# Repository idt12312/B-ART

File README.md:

# 概要
B-ARTはXbee ZigBeeモジュールみたいにUARTを無線で飛ばすモジュールです。
マイコンのプログラムを追加で書くことなく、UARTのTXとRXだけをつなげるだけでUARTを無線化できます。
無線部分はBLE(Bluetooth Low Energy)で実装をしています。

非常に小さいことが特徴で、**開発中の基板に挿して簡単に使える無線モジュール**をコンセプトに開発をしています。
(現状、秋月で買えるどの無線モジュールよりも小さいはず)

B-ARTにはType-PとType-Uの2種類があり、Type-Pはピンヘッダ、Type-UはUSBコネクタがついています。
Type-Pには4pinのピンヘッダが付いていて、3.3V-GND-TX-RX
の4本を接続するだけで使うことができます。
Type-UにはPCに直接挿せるUSBコネクタと、FTDIのUSB-UART変換IC(FT234XD)が載っています。
FT234XDのおかげでPCにさすとシリアルポートとして認識されるので、
普段シリアルポートを使うときと全く変わることなく使うことができます。

B-ARTの裏面にはType-P、Type-UともにDIPスイッチがあり、そこからIDを設定できます。
IDが同じ相手を選択して通信をするので、同じ環境にB-ARTが何組もあってもIDさえ違えば混線が起きないようになっています。

## 使用例
例えば小さい走行ロボットを無線を使ってデバッグする時にB-ARTは役立つでしょう。
走行をさせるときに有線だと線が邪魔になり、Xbeeなどはモジュールが大きすぎて載せられないという状況です。

下の写真は現在制作中のマイクロマウスの機体[MIZUHOv2](http://idken.net/posts/2017-04-01-mizuhov2/)に
B-ART TypePを挿しているところです。

B-ARTは非常に小さく軽いので、マイクロマウスの機体に乗せても走行時にそれほど問題にはなりません。
基板に4pinのコネクタさえつけておけばほしい時にだけB-ARTを挿して使うことができます。

# 使い方

## DIPスイッチの設定

B-ARTのType-PとType-Uの基板の裏にはDIPスイッチが4bit分あり、
1bitはクライアント動作をするかサーバー動作をするか、3bitはIDを意味していています。

| DIPスイッチ | 意味                     |
|-------------|--------------------------|
| 1           | 0:client動作  1:server動作 |
| 2           | ID  bit2                   |
| 3           | ID  bit1                   |
| 4           | ID  bit0                   |

B-ARTは通信においてはType-PであるかType-Uであるかは関係なく、
同じIDを持つサーバーとクライアントが1対1で通信できるという仕組みになっています。
なので、同じIDを持っていさえすれば、

* TypeU <-> TypeU
* TypeP <-> TypeP
* TypeU <-> TypeP

の全ての組み合わせで通信が可能です。

## TypePのセットアップ
4pinのピンヘッダ(というよりスルーホール)があり、それぞれのpinは次のような意味を持っています。

B-ARTは最大30mAくらいの電流を必要とするので、それに耐えられるような電源につないでください。

**電源・IOの電圧は3.3Vであることに注意してください**

## TypeUのセットアップ
パソコンのUSBに挿すだけです。

## 電源を入れる
電源を入れると
クライアント動作に設定されているB-ARTは赤色LEDが、
サーバー動作に設定されているB-ARTは緑色のLEDが光ります。

## サーバーとクライアントの接続
サーバー側とクライアント側に同じIDを持たせた状態で電源を入れると自動的に接続されます。
接続された瞬間にB-ARTに乗っている緑と赤の両方のLEDが一瞬点滅します。

一旦切断されても、接続可能な状態になると自動で接続されます。

## データを送受信する
UARTにデータを流すとサーバー側、クライアント側どちらからでももう片方に送信されます。
その際にLEDが点滅するので、LEDを見ることで正常に動作しているかが分かります。

### UARTの通信仕様

以下の設定でのみ動作します。

| パラメータ     | 値 |
|--------------|-----------|
| Baudrate     | 115200bps |
| Data size    | 8bit      |
| Start bit    | 1bit      |
| Stop bit     | 1bit      |
| Parity       | なし       |
| Flow control | なし       |
| 信号レベル      | 3.3V      |

※UART側からデータを連続して送り続けると、データが欠損する可能性があります。
確実に連続して送信できるのは70byteくらいです。
それ以上のデータが連続する場合は、70byteくらいごとに間隔をあけてください。

# 基板

### TypeP

回路図

アートワーク

### TypeU

USB周りの回路図

マイコン周りの回路図

アートワーク

# ファームウェア

## 最新のファームウェアのバイナリ

最新のビルドされたバイナリはbinディレクトリに入っています。

## 開発環境

* [Nordic nRF5 SDK v12.1](https://www.nordicsemi.com/eng/Products/Bluetooth-low-energy/nRF5-SDK)
* Nordic SoftDevice S130
* [Eclipse Juno](https://eclipse.org/)
* [Eclipse CDT](https://eclipse.org/cdt/)
* [GNU ARM Eclipse Plugin](http://gnuarmeclipse.github.io/)
* [gcc-arm-none-eabi-4_9-2015q3](https://launchpad.net/gcc-arm-embedded/4.9/4.9-2015-q3-update)

Eclipseのプロジェクトごとリポジトリにあげてあるので、
きっとEclipseにimportするだけで動かすことができます。

## 動作
起動時にDIPスイッチの状態を読み取って(main.c)、サーバー動作(main_server.c)をするか、
クライアント動作(main_client.c)をするかを決定しています。

BLEの操作はNordicのサンプルにある、NUSを参考にしています。
SDKにあるble_nusとble_nus_cをもとにble_bartsとble_barts_cを書いています。(名前を変えただけ)

### サーバー動作

GATTサーバーとして、次のようなサービスを立てます。

| AttributeType  | Name        | Permissions | UUID                                 |
|----------------|-------------|-------------|--------------------------------------|
| Service        | BART Service | Read       | 20yy0001-DA04-4C71-ADBE-6CA269E7E983 |
| Characteristic | TX          | Write       | 20yy0002-DA04-4C71-ADBE-6CA269E7E983 |
| Characteristic | RX          | Notify      | 20yy0003-DA04-4C71-ADBE-6CA269E7E983 |

TXにwriteするとUARTからデータが出力され、
UARTにデータが入るとRXをsubscribeしているデバイスにNotifyします。

UUIDのyyはID(3bit)を16進数に変換したものが入ります。

### クライアント動作
自分と同じIDをもつサーバーを探します。
このとき、サーバーのもつServiceのUUID(上の表のyy)をもとに同じIDのものを検索します。

同じIDのサーバーが見つかったらConnectし、RXのCharactericics(notify)をsubscribeします。

後はUARTからデータが来たらサーバーのRXにwriteをし、サーバーからnotifyが来たらUARTにデータを流します。

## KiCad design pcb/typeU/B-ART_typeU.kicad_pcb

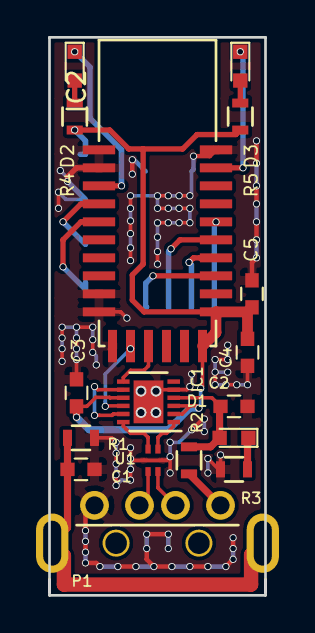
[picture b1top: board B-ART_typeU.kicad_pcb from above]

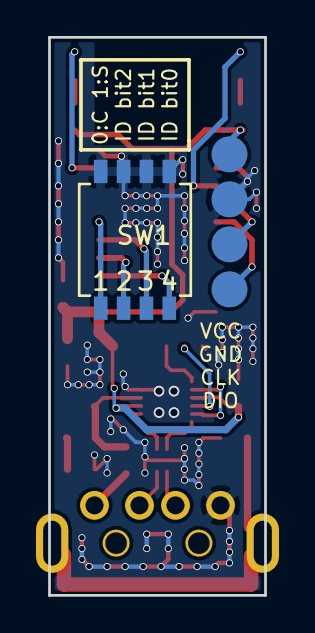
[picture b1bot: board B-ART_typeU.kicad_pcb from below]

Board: 2 copper layers, 12.0 x 31.0 mm, 22 parts (5 on the bottom side), 23 nets.

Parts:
C1, C2, C3, C5: 0.1u; C_0603
C4: 10u; C_0603
D1: Blue; LED_0603
D2: RED; LED_0603
D3: GREEN; LED_0603
IC1: FT234XD; DFN-12-1EP_3x3mm_Pitch0.45mm
IC2: BVMCN5103-BK
P1: USB_A; USB_A_plug
R1, R2: BLM18P; R_0603
R3, R4: 1k; R_0603
R5: 510; R_0603
SW1: DIPSW-4; DIPSW-4P
U1: LXES11D
W1: VCC; test_th_pad
W2: GND; test_th_pad
W3: SWDCLK; test_th_pad
W4: SWDIO; test_th_pad

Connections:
+3V3: C3.1, C4.1, C5.1, IC1.2, IC1.3, IC1.9, IC2.16, IC2.17, R4.1, R5.1, W1.1
/RX: IC1.7, IC2.13
/SW1: IC2.22, SW1.1
/SW2: IC2.20, SW1.2
/SW3: IC2.21, SW1.3
/SW4: IC2.19, SW1.4
/TX: IC1.10, IC2.12
GND: C1.2, C2.2, C3.2, C4.2, C5.2, IC1.5, IC1.13, IC2.1, IC2.2, IC2.9, IC2.10, IC2.11, IC2.26, P1.4, R1.2, R3.2, SW1.5, SW1.6, SW1.7, SW1.8, U1.3, U1.6, W2.1
unnamed: C1.1, P1.5, R1.1
unnamed: C2.1, D1.2, IC1.4, R2.1
unnamed: D1.1, R3.1
unnamed: D2.1, IC2.3
unnamed: D2.2, R4.2
unnamed: D3.1, IC2.25
unnamed: D3.2, R5.2
unnamed: IC1.1, U1.1
unnamed: IC1.8, IC1.11
unnamed: IC1.12, U1.2
unnamed: IC2.4, W3.1
unnamed: IC2.5, W4.1
unnamed: P1.1, R2.2
unnamed: P1.2, U1.5
unnamed: P1.3, U1.4

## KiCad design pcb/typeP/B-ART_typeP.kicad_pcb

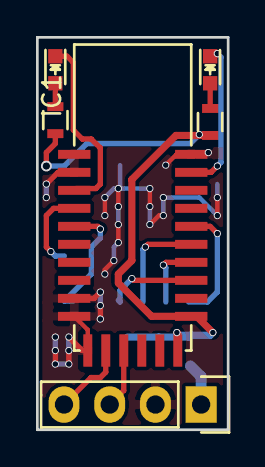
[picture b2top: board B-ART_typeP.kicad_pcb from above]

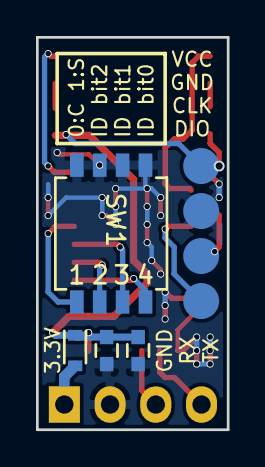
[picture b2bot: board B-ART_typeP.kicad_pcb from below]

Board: 2 copper layers, 10.6 x 21.8 mm, 14 parts (8 on the bottom side), 15 nets.

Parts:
C1: 10u; C_0603
C2: 0.1u; C_0603
D1: RB520S; D_0603
D2: RED; LED_0603
D3: GREEN; LED_0603
IC1: BVMCN5103-BK
P1: CONN_01X04; Pin_Header_Straight_1x04
R1: 1k; R_0603
R2: 510; R_0603
SW1: DIPSW-4; DIPSW-4P
W1: VCC; test_th_pad
W2: GND; test_th_pad
W3: SWDCLK; test_th_pad
W4: SWDIO; test_th_pad

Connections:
+3V3: C1.1, C2.1, D1.1, IC1.16, IC1.17, R1.1, R2.1, W1.1
/RX: IC1.13, P1.3
/SW1: IC1.22, SW1.1
/SW2: IC1.20, SW1.2
/SW3: IC1.21, SW1.3
/SW4: IC1.19, SW1.4
/TX: IC1.12, P1.4
GND: C1.2, C2.2, IC1.1, IC1.2, IC1.9, IC1.10, IC1.11, IC1.26, P1.2, SW1.5, SW1.6, SW1.7, SW1.8, W2.1
unnamed: D1.2, P1.1
unnamed: D2.1, IC1.3
unnamed: D2.2, R1.2
unnamed: D3.1, IC1.25
unnamed: D3.2, R2.2
unnamed: IC1.4, W3.1
unnamed: IC1.5, W4.1

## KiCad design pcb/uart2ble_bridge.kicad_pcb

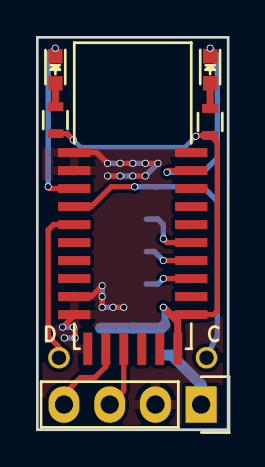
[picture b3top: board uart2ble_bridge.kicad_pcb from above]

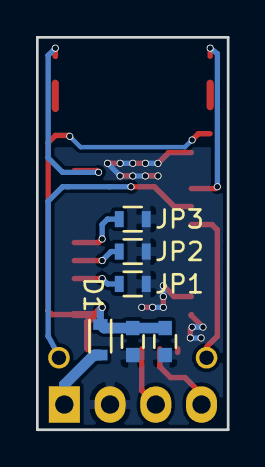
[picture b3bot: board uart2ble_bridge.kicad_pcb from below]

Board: 2 copper layers, 10.6 x 21.8 mm, 14 parts (6 on the bottom side), 14 nets.

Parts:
C1: 10u; C_0603
C2: 0.1u; C_0603
D1: RB520S; D_0603
D2: RED/OSHR1608; LED_0603
D3: GREEN/OSYG1608; LED_0603
JP1, JP2, JP3: 0; R_0603
P1: CONN_01X04; Pin_Header_Straight_1x04
P2: SWDCLK; test_th_pad
P3: SDWIO; test_th_pad
R1: 330; R_0603
R2: 220; R_0603
U1: BVMCN5103-BK

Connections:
+3V3: C1.1, C2.1, D1.1, R1.1, R2.1, U1.16, U1.17
/RX: P1.3, U1.13
/TX: P1.4, U1.12
GND: C1.2, C2.2, JP1.1, JP2.1, JP3.1, P1.2, U1.1, U1.2, U1.9, U1.10, U1.11, U1.26
unnamed: D1.2, P1.1
unnamed: D2.1, U1.3
unnamed: D2.2, R1.2
unnamed: D3.1, U1.25
unnamed: D3.2, R2.2
unnamed: JP1.2, U1.19
unnamed: JP2.2, U1.20
unnamed: JP3.2, U1.21
unnamed: P2.1, U1.4
unnamed: P3.1, U1.5

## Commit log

2016-11-27 基板データを作成
2016-11-28 nordic SDK v12.1 + Eclipse で開発環境を構築 uart2bleのサービスを実装(nusとほとんど同じ)
2016-11-28 図面のプロパティを設定
2016-11-29 LEDを二つともマイコンから操作できるように変更
2016-11-29 LEDの操作を追加
2016-12-27 firm 裏面のジャンパーピンを参照してdevice idを決定する部分を実装
2016-12-27 firm LEDの光りかたを微調整
2017-01-15 アドバタイズに含めるserviceのUUIDを修正
2017-01-25 クライアントの処理を追加
    NUS_Cのサンプルを模倣
2017-01-29 クライアント側でBLEのイベントをdb_discoveryに通知し忘れていたので修正
2017-01-29 送信強度を4dB(最大)に設定
2017-01-29 LED, デバッグ出力周りを修正
2017-02-09 USB付き基板を追加 + 以前の基板も修正
2017-02-11 新しい基板に合わせてIOピン周りを修正
2017-03-08 firm_server: アドバタイズに乗せるServiceのUUIDの設定が間違っていたので修正
2017-03-08 firm_server: アドバタイズがタイムアウトしても再度アドバタイズを出すように修正
2017-03-09 firm: BLEが未接続時にはUARTのデータを無視する処理を追加
2017-03-27 firm: Eclipseのプロジェクト名を変更
    bleのサービス名もB-ARTに変更
2017-03-27 pcb: KiCadのプロジェクト名を変更
2017-03-27 Create LICENSE
2017-04-01 ライブラリが除外されていたので追加
2017-04-01 回路図を成形 & 回路図pdfを追加
2017-04-04 ドキュメントを追加
2017-04-04 画像へのリンクを修正
2017-04-04 READMEを修正
2017-04-04 READMEの画像をサイズを縮小
2017-08-08 firm: BandwidthとConnection Intervalを調整
2017-08-10 firm: クロックの設定を修正
    HFCLKには外部のXTALを使う設定に
2017-08-10 Connection IntervalごとにUARTから受信したデータを送るように変更
    ・UARTの受信イベントで得たデータはいったんFIFOに貯めておき、BLEのパケットが送信されるごとに送れるだけ送る実装に変更
    ・UARTの割り込み優先度を上げた
    ・115200bpsで80byteくらいまでしか連続で送れない
2017-08-10 firm: ファームのバイナリをbinに追加
2017-08-11 READMEを更新
